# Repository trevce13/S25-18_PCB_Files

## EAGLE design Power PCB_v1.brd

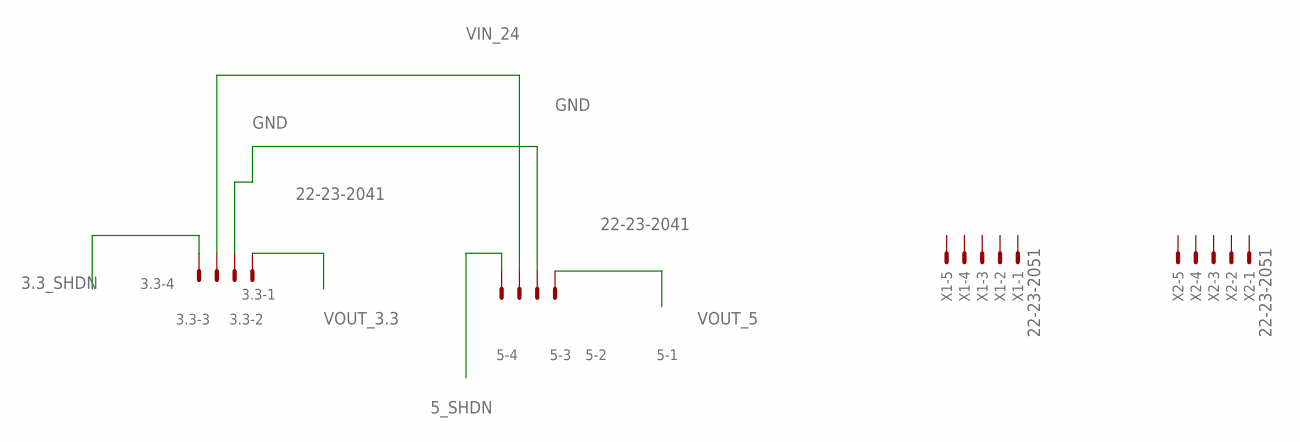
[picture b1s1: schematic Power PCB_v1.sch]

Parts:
3.3, 5: 22-23-2041
X1, X2: 22-23-2051

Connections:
3.3_SHDN: 3.3.4
5_SHDN: 5.4
GND: 3.3.2, 5.2
VIN_24: 3.3.3, 5.3
VOUT_3.3: 3.3.1
VOUT_5: 5.1

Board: 2 copper layers, 4 parts (0 on the bottom side), 2 nets, no tracks yet.

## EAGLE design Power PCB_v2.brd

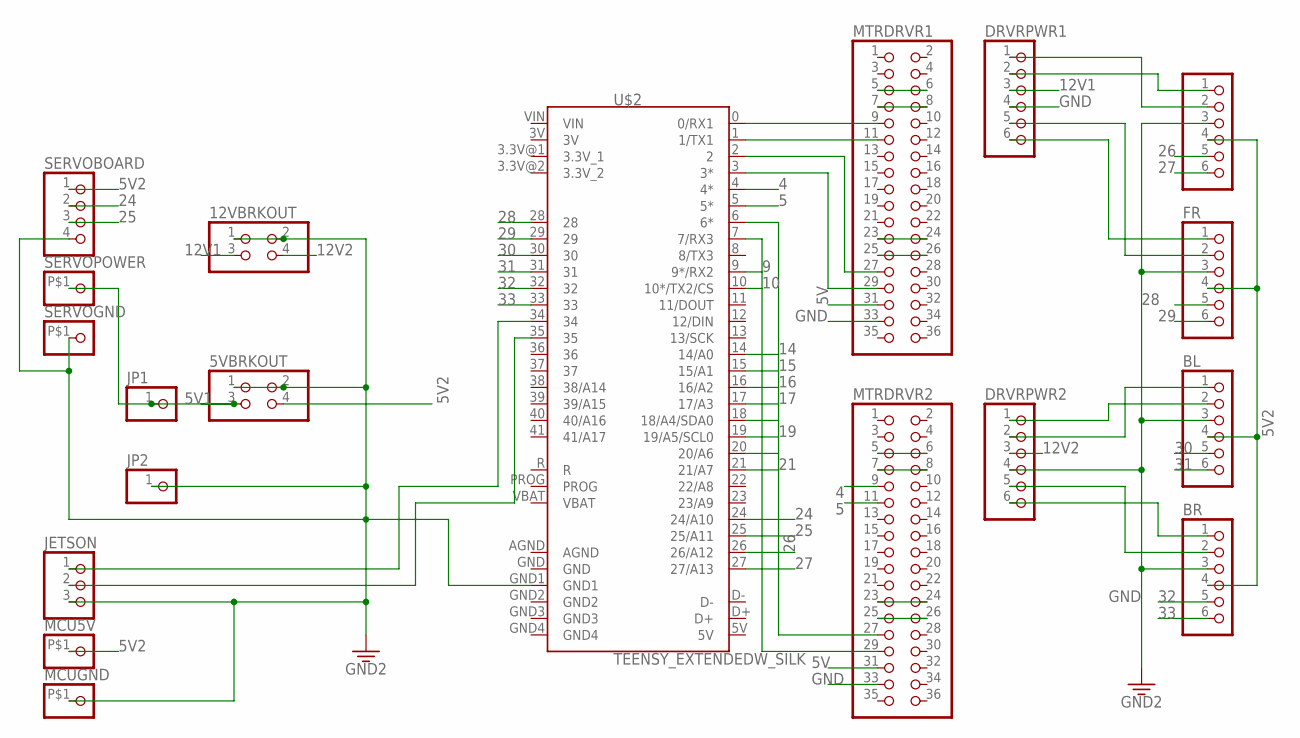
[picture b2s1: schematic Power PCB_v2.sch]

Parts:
5VBRKOUT, 12VBRKOUT: PINHD-2X2; 2X02
BL: PINHD-1X6; 1X06
BR: PINHD-1X6; 1X06
DRVRPWR1, DRVRPWR2: PINHD-1X6-3.5MM; 1X06-3.5MM
FL: PINHD-1X6; 1X06
FR: PINHD-1X6; 1X06
JETSON: PINHD-1X3; 1X03
JP1, JP2: PINHD-1X1; 1X01
MCU5V: PINHD-1X1-BIGPOGO; 1X1-BIGPOGO
MCUGND: PINHD-1X1-BIGPOGO; 1X1-BIGPOGO
MTRDRVR1, MTRDRVR2: PINHD-2X18; 2X18
SERVOBOARD: PINHD-1X4; 1X04
SERVOGND: PINHD-1X1-BIGPOGO; 1X1-BIGPOGO
SERVOPOWER: PINHD-1X1-BIGPOGO; 1X1-BIGPOGO
U$2: TEENSY_EXTENDEDW_SILK; TEENSY_EXTENDED

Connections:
3.3V_1: U$2.3.3V@1 (3.3V_1)
3.3V_2: U$2.3.3V@2 (3.3V_2)
3V: U$2.3V
4: MTRDRVR2.9, U$2.4 (4*)
5: MTRDRVR2.11, U$2.5 (5*)
5V: MTRDRVR1.31, MTRDRVR2.31, U$2.5V
5V1: 5VBRKOUT.3, JP1.1, SERVOPOWER.P$1
5V2: 5VBRKOUT.4, BL.4, BR.4, FL.4, FR.4, MCU5V.P$1, SERVOBOARD.1
9: U$2.9 (9*/RX2)
10: U$2.10 (10*/TX2/CS)
12V1: 12VBRKOUT.3, DRVRPWR1.3
12V2: 12VBRKOUT.4, DRVRPWR2.3
14: U$2.14 (14/A0)
15: U$2.15 (15/A1)
16: U$2.16 (16/A2)
17: U$2.17 (17/A3)
18: U$2.18 (18/A4/SDA0)
19: U$2.19 (19/A5/SCL0)
20: U$2.20 (20/A6)
21: U$2.21 (21/A7)
24: SERVOBOARD.2, U$2.24 (24/A10)
25: SERVOBOARD.3, U$2.25 (25/A11)
26: FL.5, U$2.26 (26/A12)
27: FL.6, U$2.27 (27/A13)
28: FR.5, U$2.28
29: FR.6, U$2.29
30: BL.5, U$2.30
31: BL.6, U$2.31
32: BR.5, U$2.32
33: BR.6, U$2.33
AGND: U$2.AGND
D+: U$2.D+
D-: U$2.D-
GND: 5VBRKOUT.1, 5VBRKOUT.2, 12VBRKOUT.1, 12VBRKOUT.2, BL.3, BR.3, DRVRPWR1.4, DRVRPWR2.4, FL.3, FR.3, JETSON.3, JP2.1, MCUGND.P$1, MTRDRVR1.5, MTRDRVR1.6, MTRDRVR1.33, MTRDRVR2.33, SERVOBOARD.4, SERVOGND.P$1, U$2.GND, U$2.GND1
GND2: U$2.GND2
GND3: U$2.GND3
GND4: MTRDRVR2.5, MTRDRVR2.6
unnamed: DRVRPWR1.2, FL.1
unnamed: MTRDRVR1.9, U$2.0 (0/RX1)
unnamed: MTRDRVR2.7, MTRDRVR2.8
unnamed: MTRDRVR1.7, MTRDRVR1.8
unnamed: DRVRPWR1.1, FL.2
unnamed: MTRDRVR1.11, U$2.1 (1/TX1)
unnamed: MTRDRVR1.23, MTRDRVR1.24
unnamed: MTRDRVR2.25, MTRDRVR2.26
unnamed: MTRDRVR1.29, U$2.3 (3*)
unnamed: MTRDRVR2.23, MTRDRVR2.24
unnamed: JETSON.1, U$2.34
unnamed: DRVRPWR1.5, FR.2
unnamed: DRVRPWR1.6, FR.1
unnamed: MTRDRVR1.27, U$2.2
unnamed: BL.1, DRVRPWR2.2
unnamed: BL.2, DRVRPWR2.1
unnamed: BR.1, DRVRPWR2.6
unnamed: BR.2, DRVRPWR2.5
unnamed: MTRDRVR1.25, MTRDRVR1.26
unnamed: JETSON.2, U$2.35
unnamed: MTRDRVR2.27, U$2.6 (6*)
unnamed: MTRDRVR2.29, U$2.7 (7/RX3)
VBAT: U$2.VBAT
VIN: U$2.VIN

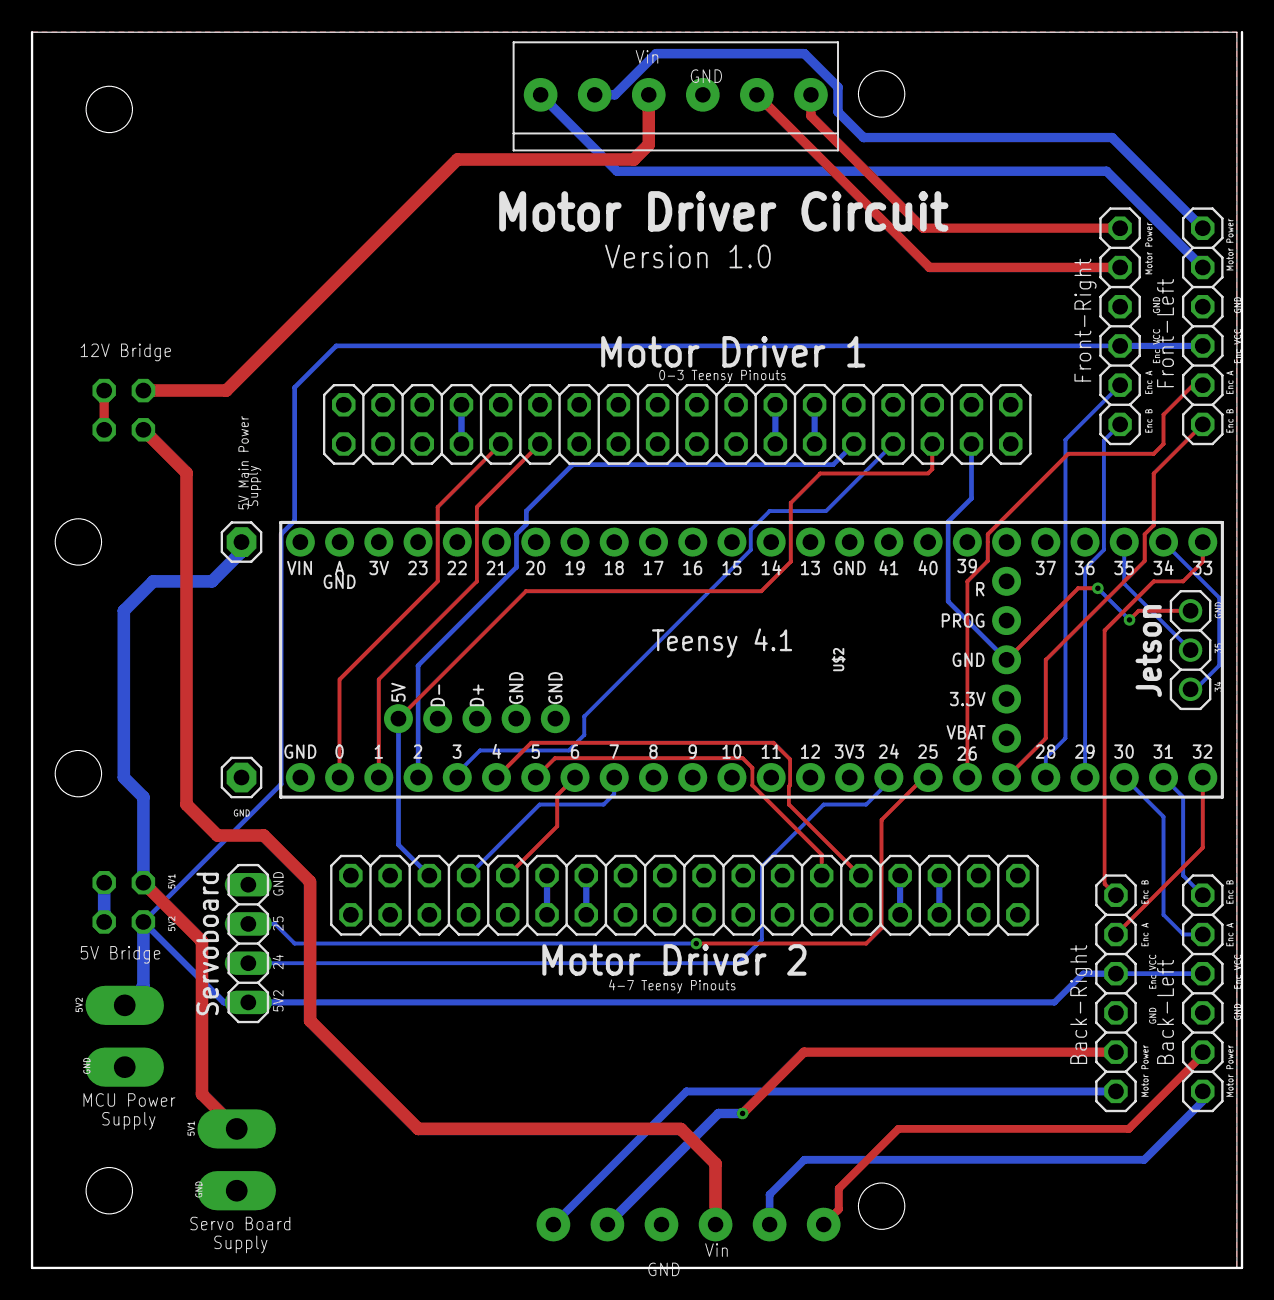
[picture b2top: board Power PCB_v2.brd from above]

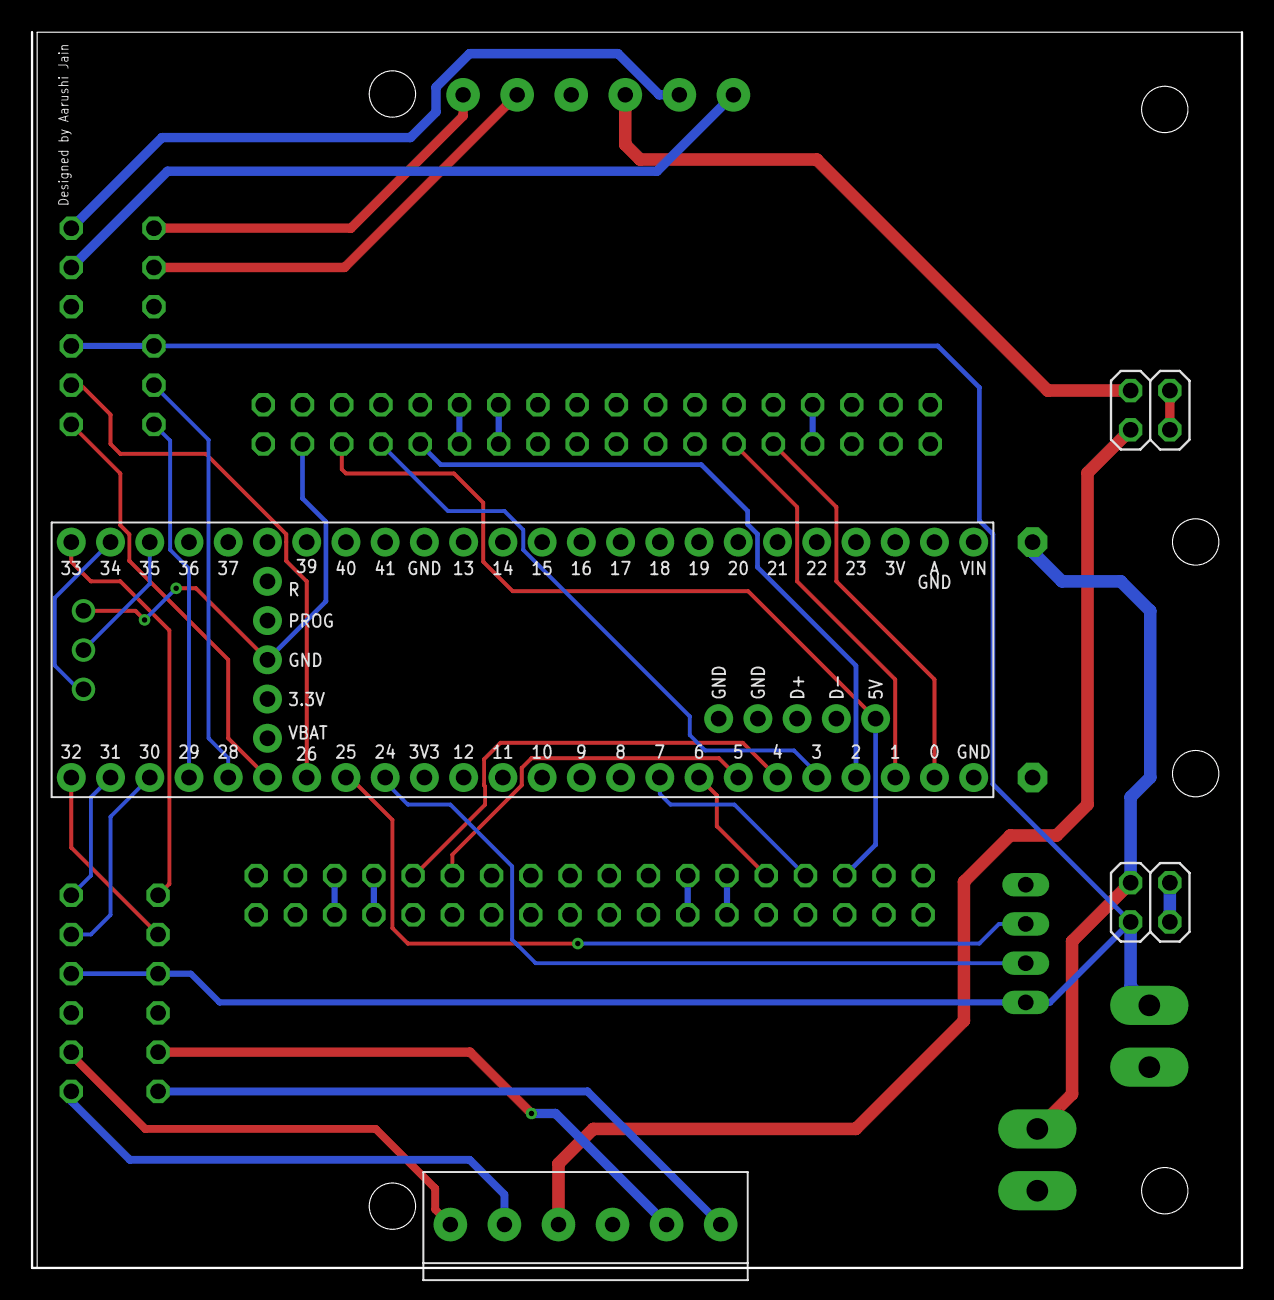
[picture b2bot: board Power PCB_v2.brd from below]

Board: 2 copper layers, 78.0 x 80.0 mm, 19 parts (3 on the bottom side), 41 nets.

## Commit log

2025-01-31 Sensor PCBs First Drafts
2025-02-26 Sensor PCB Files
2025-02-26 Power PCB files (Most recent v7)
2025-02-26 Control PCB files (most recent v3)
2025-02-26 Custom Components and libraries needed
2025-03-03 Most recent files Power v8 , control v4, sensors v5
2025-03-03 Recent power v9, control, v5
2025-03-03 Control v6
2025-03-04 PCBs ready for reviewal before ordering Power v10, control v7, sensor v6

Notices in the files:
parts and their libraries:
SparkFun-Boards: Licensing: Creative Commons ShareAlike 4.0 International - https://creativecommons.org/licenses/by-sa/4.0
